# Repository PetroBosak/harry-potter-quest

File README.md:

# Квест «Гаррі Поттер» — Сортувальний капелюх

Нова електроніка для шапки зі старого квесту. Плата та сама, що в щитах LaserX «6-7»
(репозиторій [challenge-duel](https://github.com/PetroBosak/challenge-duel), варіант плати `hat`),
плюс вихід на мотор «рота».

## Що робить шапка
Так само, як стара прошивка (`ref/hate_hogrards.ino`, Arduino + DFPlayer + реле):

| Кнопка брелока | Фрази (по колу) | Світло |
|---|---|---|
| Грифіндор | 0001…0007 | червоний з золотими іскрами |
| Слизерин | 0008…0014 | зелений зі срібними іскрами |
| Старт | 0015…0016 | фіолетовий / синій |
| Фінал | 0017…0018 | золотий |

- Мотор ворушить «рот» у такт фразі за таблицями зі старої прошивки (`firmware/hat/mouth.h`).
  Замість реле тепер транзистор: плавний старт (ШІМ 20 кГц), потужність задається в `config.h`.
- Нова кнопка брелока перебиває поточну фразу.
- **Кнопка на шапці** (J3): замовкнути (звук, мотор і світло зупиняються).
- Чекаючи, капелюх ледь «дихає» фіолетовим (якщо підключена стрічка).
- Коди старого брелока вже вписані, тож він працює одразу. **Інший брелок:** увімкнути шапку
  з затиснутою кнопкою, далі натиснути на брелоку по черзі Грифіндор → Слизерин → Старт → Фінал.
  Після кожної кнопки мотор коротко смикнеться, коди збережуться в пам'яті.

## Залізо
- Плата: [`pcb/`](pcb/) — гербери для замовлення, BOM, схема, KiCad (50×50 мм): ESP32-C3 SuperMini, MAX98357A,
  приймач SYN480R, ключ мотора AO3400A на GPIO20 з захисним діодом SS34.
- Схема підключення: [`docs/wiring-hat.png`](docs/wiring-hat.png) (генерує `docs/tools/wiring_hat.py`).
- Та сама плата йде й на **мандрагору** (пищалка, коли піднімають іграшку): модуль заряду J5019 на звороті,
  клемники АКУМ і ЗАРЯДКА — див. [`pcb/README.md`](pcb/README.md#мандрагора-живлення-від-акумулятора).
- Роз'єми: J1 блок 5 В (**XT30PW-M** на платі, XT30U-F на дроті блока; захисту від переполюсовки немає) ·
  клемники J2 стрічка WS2812B · J3 кнопка · J4 друга стрічка (необов'язково) · **J5 МОТОР (M+ / M−)** ·
  J6 передавач FS1000A (TX = GPIO21, 5V, GND; на майбутнє, прошивка його не використовує) ·
  динамік — у клеми модуля MAX98357A.
- C1 — SMD-електроліт 1000 мкФ 10 В, 10×10,5 мм (Hitano ELV102M10RF): конденсатор із виводами на цю плату не встане.
- Замовлення: панель 2×2 `pcb/panel-hat-gerber.zip` або одна плата `pcb/shield67-hat-gerber.zip`; деталі й пайка — [`pcb/README.md`](pcb/README.md).
- Мотор **на 5 В** (підтверджено замовником), живиться від +5 В блока. Ключ витримує кілька ампер.

## Звуки
Звуки вбудовані в прошивку, SD-картка і DFPlayer не потрібні.
`firmware/sounds/0001…0018.mp3` → `python firmware/tools/gen_sounds.py` → `firmware/hat/sounds.h`
(IMA ADPCM, 16 кГц; усі 18 фраз ≈ 1,5 МБ). Потрібен `ffmpeg`.
Новий трек: покласти mp3 з потрібним номером, перегенерувати `sounds.h`, за потреби поправити `mouth.h`
і групи в `config.h`, перепрошити.

## Прошивка
Бібліотеки: **FastLED 3.9.20** (не 3.10.x, вона не компілюється під C3), **rc-switch**.
Ядро `esp32:esp32` (3.x або 2.0.17).

```bash
arduino-cli compile --fqbn esp32:esp32:esp32c3:PartitionScheme=huge_app,CDCOnBoot=cdc --upload -p COMx firmware/hat
```

Монітор: `arduino-cli monitor -p COMx -c baudrate=115200`. Там видно коди брелока й номери фраз.
Нова SuperMini не прошивається: затиснути BOOT, натиснути й відпустити RST, відпустити BOOT.

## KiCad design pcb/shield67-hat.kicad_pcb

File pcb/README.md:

# Плата шапки (50 × 50 мм)

Плата під ESP32-C3 SuperMini — та сама, що в щитах LaserX «6-7», варіант `hat`: плюс ключ мотора «рота»,
а на звороті — місце під модуль заряду J5019 для мандрагори (від акумулятора).

| Файл | Що це |
|---|---|
| `shield67-hat-gerber.zip` | **для замовлення** (JLCPCB, PCBWay…): завантажити zip як є, 2 шари, 1,6 мм |
| `gerber-hat/` | ті самі гербери й свердління, розпаковані |
| `BOM-hat.csv` | список деталей |
| `shield67-hat-schematic.pdf` | принципова схема |
| `render-top-hat.png`, `render-bottom-hat.png`, `routing-hat.png` | як виглядає плата і доріжки |
| `shield67-hat.kicad_*`, `lib/`, `*-lib-table` | проєкт KiCad 10 (відкривати `shield67-hat.kicad_pro`) |

## Замовлення: панель 2×2 = 4 плати на 100×100 мм
Мінімальне замовлення 5 шт. → 5 панелей = **20 плат** — на всі атракціони (шапка, щити тощо: та сама плата, різні деталі розпаюються).

| Файл | Що це |
|---|---|
| `panel-hat-gerber.zip` | **для замовлення панеллю** |
| `gerber-panel-hat/`, `panel-hat.kicad_pcb` | те саме розпаковане / KiCad |
| `render-top-panel-hat.png` | як виглядає панель |

Як замовляти на JLCPCB: завантажити `panel-hat-gerber.zip`, розмір визначиться **100 × 100 мм**, далі
**Delivery Format / Panel: «Panel by Customer»**, **Panel Format: V-cut** (лінії V-cut — посередині по x і y, у шарі контуру),
кількість **5**. Шари 2, товщина 1,6 мм, решта — за замовчуванням.
Мідь від лінії V-cut — 0,5 мм (вимога JLCPCB ≥ 0,4). Плати ламаються руками по V-cut, потім паяються.

Під щит «6-7» мотор не потрібен: Q1, R7, R8, D2, C5, J5 не паяти. На шапці й щитах U6, J7, J8 (зворот) не паяти.

## Роз'єми
| | Що підключати |
|---|---|
| **J1** XT30PW-M | блок живлення **5 В** (на дроті — XT30U-F). Захисту від переполюсовки немає |
| **J2** | стрічка WS2812B (GPIO10) |
| **J3** | кнопка на шапці (GPIO5 → GND) |
| **J4** | друга стрічка (GPIO7), необов'язково |
| **J5 МОТОР** | M+ = +5 В, M− = ключ Q1 AO3400A (GPIO20), діод SS34 паралельно мотору |
| **J6** | передавач FS1000A (TX = GPIO21, 5V, GND), на майбутнє |
| **J7** АКУМ (зворот) | лише мандрагора: акумулятор Li-ion 3,7 В, «+» — верхній вивід; вимикач — у дроті «+» |
| **J8** ЗАРЯДКА 5 В (зворот) | лише мандрагора: гніздо зарядки 5 В (на стінці відра) → IN+/IN− модуля, «+» — верхній |
| динамік | у клеми модуля MAX98357A |

Приймач — SYN480R 433 МГц, антена — дріт 17,3 см у пад **ANT**. Отворів кріплення 2 (угорі).

## Мандрагора: живлення від акумулятора

- **U6 — модуль J5019** (заряд Li-ion + підвищувач до 5 В) на **звороті**, на штирях 2,54 мм крізь 6 отворів:
  BAT−, BAT+, IN−, IN+, VOUT−, VOUT+. Отвори овальні (допуск ±0,6 мм). Відстані між отворами (виміряв замовник):
  BAT−↔BAT+ 9,2 мм, VOUT−↔VOUT+ 7,0, IN−↔IN+ 16, IN+↔VOUT− 6,8, BAT+↔VOUT− уздовж 10, ряди 20.
- Перед пайкою **роздрукувати `mandrake-back-1to1.pdf` у масштабі 100 %** і прикласти модуль: отвори мають збігтися.
- Висновки SuperMini і MAX98357A під модулем підрізати коротко; штирі модуля, що виходять на лице під модулі, — теж.
- Підвищувач J5019 **до пайки виставити на 5,0 В** (підстроювач на модулі, тестером на VOUT).
- **XT30 (J1) у мандрагорі не паяти**: це вхід 5 В на рейку плати, а не зарядка. Зарядка — тільки через **J8**.
- Пищалка (активна, 5 В) — на **J5** (M+ / M−), датчик (геркон / Холл / мікроперемикач) — на **J3**.

## Як паяти
1. Спершу SMD: U4, U5 (ключ — вивід 1), Q1, R1–R8, C2–C6, D1 і D2 (**смужка — катод**), C1.
   **C1** — SMD-електроліт 1000 мкФ 10 В, 10×10,5 мм (Hitano ELV102M10RF): **чорна мітка на корпусі — мінус, праворуч**, зрізані кути основи — до «+» ліворуч.
2. Гребінки «мама»: 2 × 1×8 (SuperMini), 1×7 (MAX98357A), 1×4 (SYN480R) — вставити в модулі й паяти разом із ними.
3. Клемники, XT30 (у мандрагорі — замість XT30 модуль J5019 і клемники J7, J8 на звороті).
4. Тестером: +5V ↔ GND немає КЗ; на 5V SuperMini після D1 ≈ 4,7 В від блока.

## Звідки файли
Плату генерує скрипт у репозиторії [challenge-duel](https://github.com/PetroBosak/challenge-duel/tree/claude/relaxed-gauss-k7b976/pcb)
(`SHIELD67_VARIANT=hat python pcb/tools/build.py --export`). Правки — там, потім скопіювати сюди файли `*-hat*`.

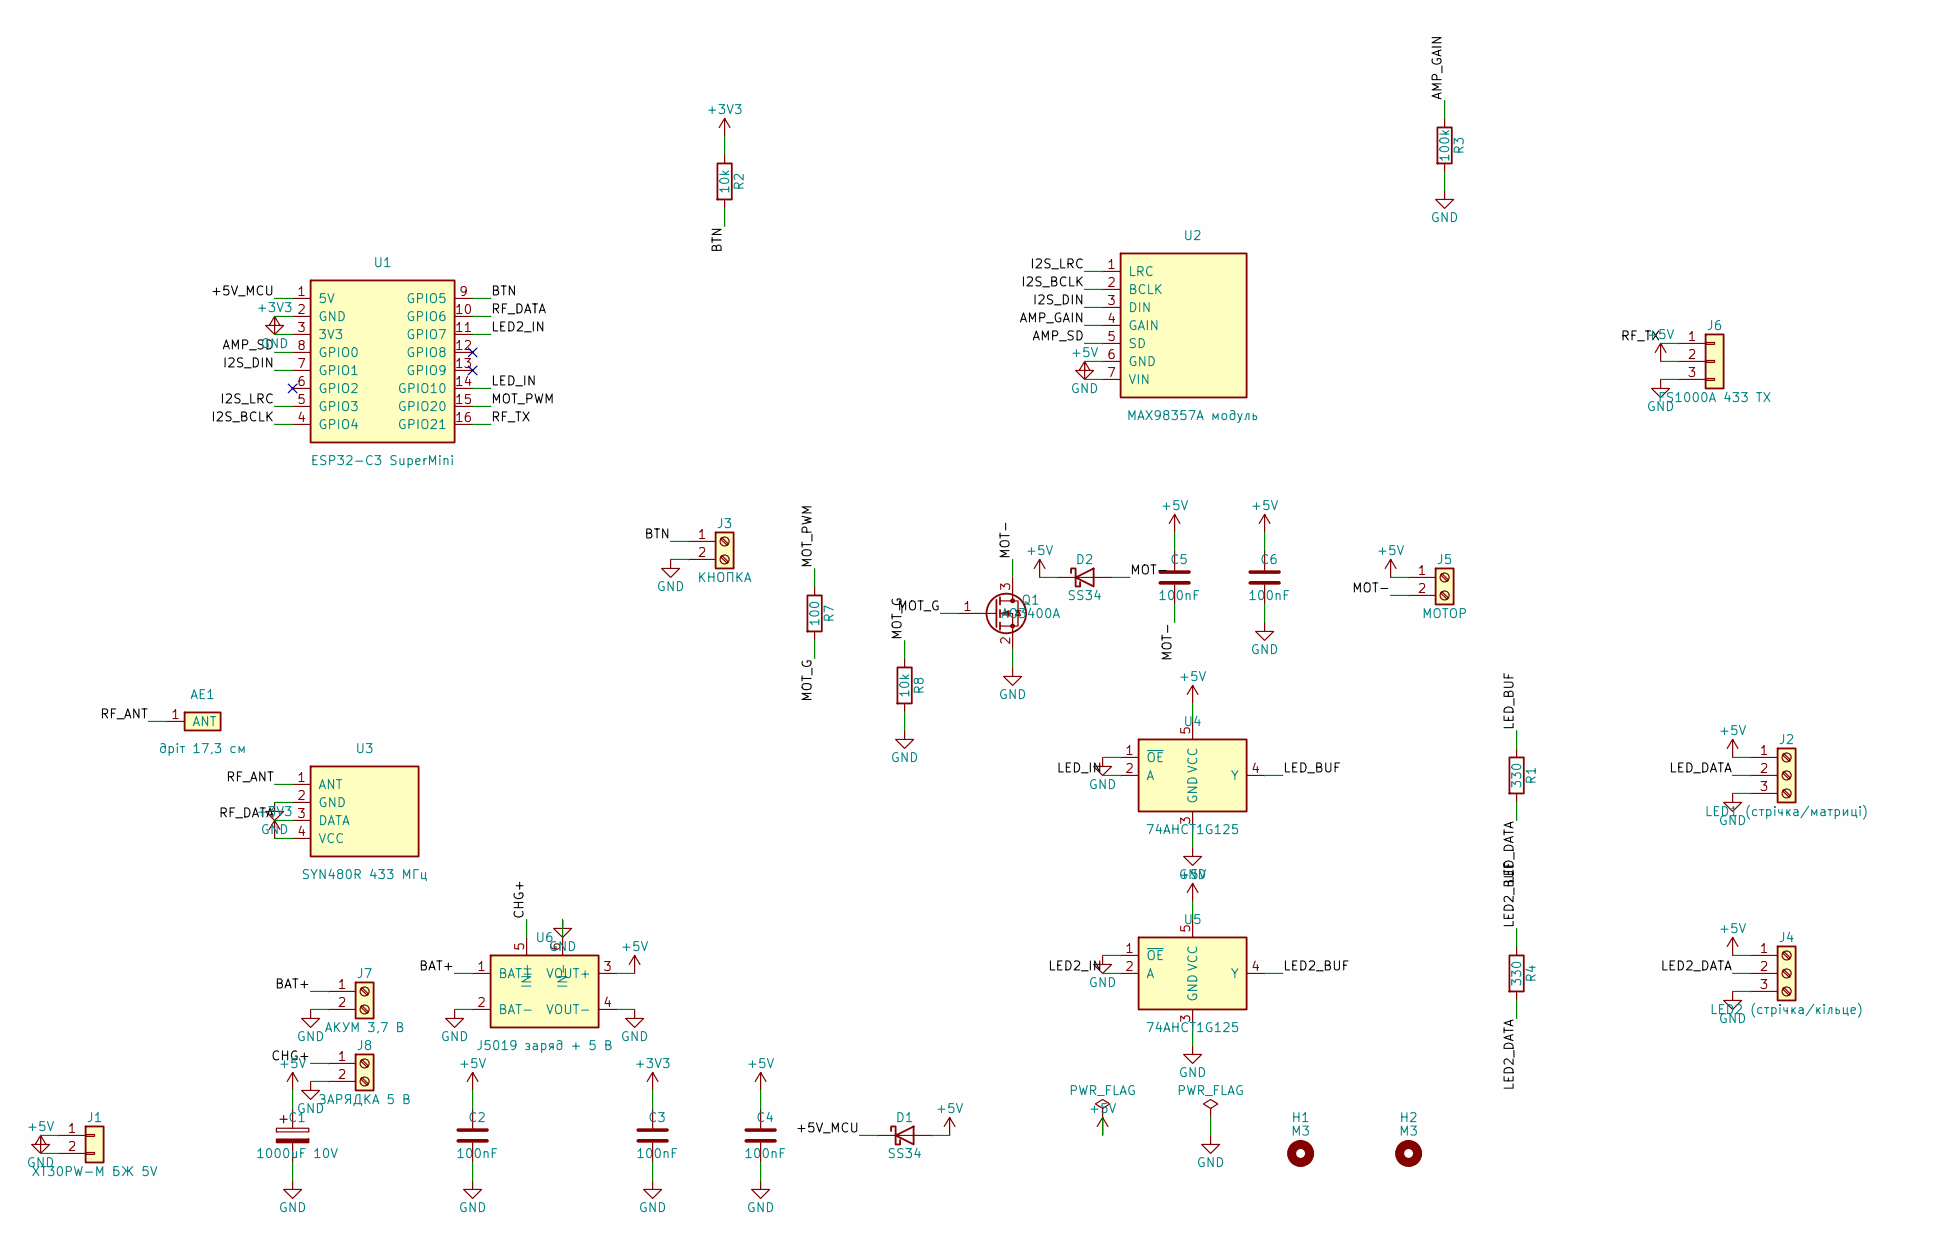
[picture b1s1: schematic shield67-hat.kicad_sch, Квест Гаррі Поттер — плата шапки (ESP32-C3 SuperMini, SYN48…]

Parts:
AE1: дріт 17,3 см; ANT_Wire_Pad
C1: 1000uF 10V; CP_Elec_10x10.5
C2, C3, C4, C5, C6: 100nF; C_0805_2012Metric
D1, D2: SS34; D_SMA
H1, H2: M3; MountingHole_3.2mm_M3
J1: XT30PW-M БЖ 5V; AMASS_XT30PW-M_1x02_P2.50mm_Horizontal
J2: LED1 (стрічка/матриці); TerminalBlock_Phoenix_PT-1,5-3-3.5-H_1x03_P3.50mm_Horizontal
J3: КНОПКА; TerminalBlock_Phoenix_PT-1,5-2-3.5-H_1x02_P3.50mm_Horizontal
J4: LED2 (стрічка/кільце); TerminalBlock_Phoenix_PT-1,5-3-3.5-H_1x03_P3.50mm_Horizontal
J5: МОТОР; TerminalBlock_Phoenix_PT-1,5-2-3.5-H_1x02_P3.50mm_Horizontal
J6: FS1000A 433 TX; PinHeader_1x03_P2.54mm_Vertical
J7: АКУМ 3,7 В; TerminalBlock_Phoenix_PT-1,5-2-3.5-H_1x02_P3.50mm_Horizontal
J8: ЗАРЯДКА 5 В; TerminalBlock_Phoenix_PT-1,5-2-3.5-H_1x02_P3.50mm_Horizontal
Q1: AO3400A; SOT-23
R1, R4: 330; R_0805_2012Metric
R2, R8: 10k; R_0805_2012Metric
R3: 100k; R_0805_2012Metric
R7: 100; R_0805_2012Metric
U1: ESP32-C3 SuperMini; ESP32-C3_SuperMini_Socket
U2: MAX98357A модуль; MAX98357A_Module_Socket
U3: SYN480R 433 МГц; SYN480R_Socket
U4, U5: 74AHCT1G125; SOT-23-5
U6: J5019 заряд + 5 В; J5019_Back

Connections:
+3V3: C3.1, R2.1, U1.3 (3V3), U3.4 (VCC)
+5V: C1.1, C2.1, C4.1, C5.1, C6.1, D1.2 (A), D2.1 (K), J1.2, J2.1, J4.1, J5.1, J6.2, U2.7 (VIN), U4.5 (VCC), U5.5 (VCC), U6.3 (VOUT+)
/+5V_MCU: D1.1 (K), U1.1 (5V)
/AMP_GAIN: R3.1, U2.4 (GAIN)
/AMP_SD: U1.8 (GPIO0), U2.5 (SD)
/BAT+: J7.1, U6.1 (BAT+)
/BTN: J3.1, R2.2, U1.9 (GPIO5)
/CHG+: J8.1, U6.5 (IN+)
/I2S_BCLK: U1.4 (GPIO4), U2.2 (BCLK)
/I2S_DIN: U1.7 (GPIO1), U2.3 (DIN)
/I2S_LRC: U1.5 (GPIO3), U2.1 (LRC)
/LED2_BUF: R4.1, U5.4 (Y)
/LED2_DATA: J4.2, R4.2
/LED2_IN: U1.11 (GPIO7), U5.2 (A)
/LED_BUF: R1.1, U4.4 (Y)
/LED_DATA: J2.2, R1.2
/LED_IN: U1.14 (GPIO10), U4.2 (A)
/MOT-: C5.2, D2.2 (A), J5.2, Q1.3 (D)
/MOT_G: Q1.1 (G), R7.2, R8.1
/MOT_PWM: R7.1, U1.15 (GPIO20)
/RF_ANT: AE1.1, U3.1 (ANT)
/RF_DATA: U1.10 (GPIO6), U3.3 (DATA)
/RF_TX: J6.1, U1.16 (GPIO21)
GND: C1.2, C2.2, C3.2, C4.2, C6.2, J1.1, J2.3, J3.2, J4.3, J6.3, J7.2, J8.2, Q1.2 (S), R3.2, R8.2, U1.2 (GND), U2.6 (GND), U3.2 (GND), U4.1 (~OE), U4.3 (GND), U5.1 (~OE), U5.3 (GND), U6.2 (BAT-), U6.4 (VOUT-), U6.6 (IN-)

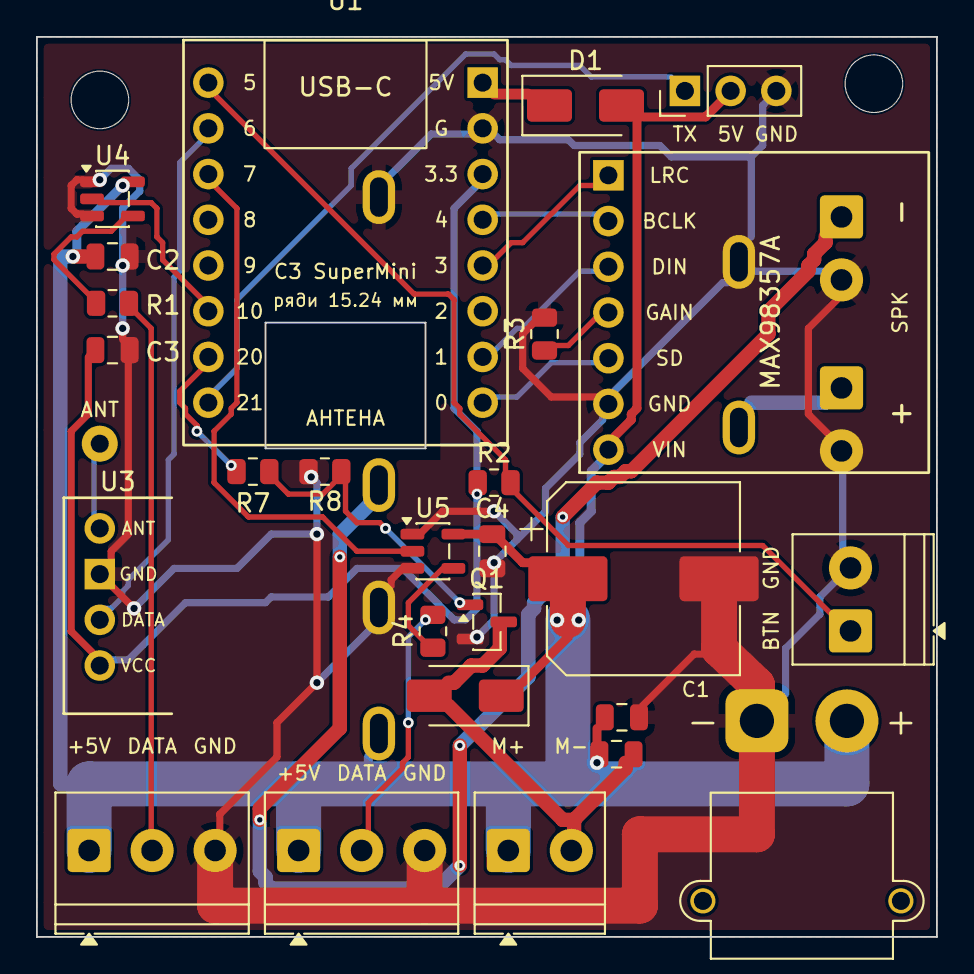
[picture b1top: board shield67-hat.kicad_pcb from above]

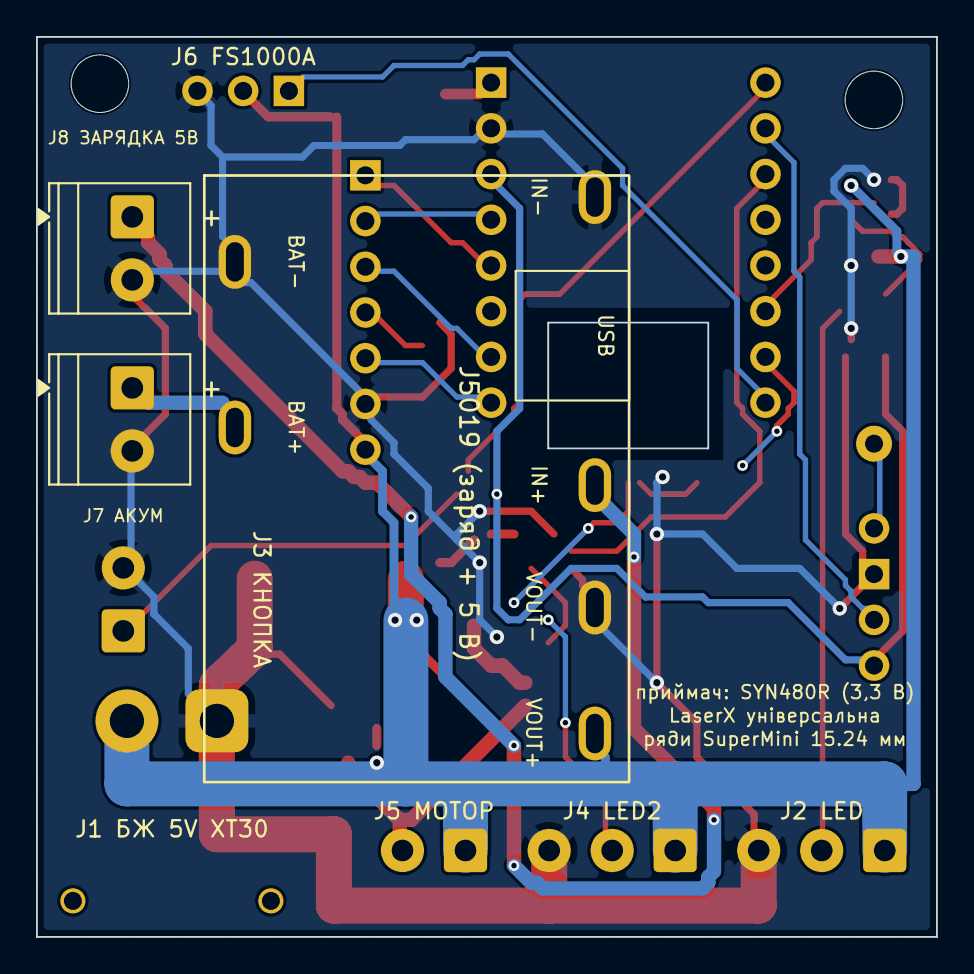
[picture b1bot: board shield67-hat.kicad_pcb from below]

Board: 2 copper layers, 50.0 x 50.0 mm, 32 parts (3 on the bottom side), 24 nets.

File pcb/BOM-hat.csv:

"Позиції","Номінал","Посадкове місце","Кількість"
"AE1","дріт 17,3 см","shield67:ANT_Wire_Pad","1"
"C1","1000uF 10V","Capacitor_SMD:CP_Elec_10x10.5","1"
"C2-C6","100nF","Capacitor_SMD:C_0805_2012Metric","5"
"D1,D2","SS34","Diode_SMD:D_SMA","2"
"J1","XT30PW-M БЖ 5V","Connector_AMASS:AMASS_XT30PW-M_1x02_P2.50mm_Horizontal","1"
"J2","LED1 (стрічка/матриці)","TerminalBlock_Phoenix:TerminalBlock_Phoenix_PT-1,5-3-3.5-H_1x03_P3.50mm_Horizontal","1"
"J3","КНОПКА","TerminalBlock_Phoenix:TerminalBlock_Phoenix_PT-1,5-2-3.5-H_1x02_P3.50mm_Horizontal","1"
"J4","LED2 (стрічка/кільце)","TerminalBlock_Phoenix:TerminalBlock_Phoenix_PT-1,5-3-3.5-H_1x03_P3.50mm_Horizontal","1"
"J5","МОТОР","TerminalBlock_Phoenix:TerminalBlock_Phoenix_PT-1,5-2-3.5-H_1x02_P3.50mm_Horizontal","1"
"J6","FS1000A 433 TX","Connector_PinHeader_2.54mm:PinHeader_1x03_P2.54mm_Vertical","1"
"J7","АКУМ 3,7 В","TerminalBlock_Phoenix:TerminalBlock_Phoenix_PT-1,5-2-3.5-H_1x02_P3.50mm_Horizontal","1"
"J8","ЗАРЯДКА 5 В","TerminalBlock_Phoenix:TerminalBlock_Phoenix_PT-1,5-2-3.5-H_1x02_P3.50mm_Horizontal","1"
"Q1","AO3400A","Package_TO_SOT_SMD:SOT-23","1"
"R1,R4","330","Resistor_SMD:R_0805_2012Metric","2"
"R2,R8","10k","Resistor_SMD:R_0805_2012Metric","2"
"R3","100k","Resistor_SMD:R_0805_2012Metric","1"
"R7","100","Resistor_SMD:R_0805_2012Metric","1"
"U1","ESP32-C3 SuperMini","shield67:ESP32-C3_SuperMini_Socket","1"
"U2","MAX98357A модуль","shield67:MAX98357A_Module_Socket","1"
"U3","SYN480R 433 МГц","shield67:SYN480R_Socket","1"
"U4,U5","74AHCT1G125","Package_TO_SOT_SMD:SOT-23-5","2"
"U6","J5019 заряд + 5 В","shield67:J5019_Back","1"
"U1","Гребінка мама 1x8, крок 2,54, пряма","—","2"
"U2","Гребінка мама 1x7, крок 2,54, пряма","—","1"
"U3","Гребінка мама 1x4, крок 2,54, пряма","—","1"

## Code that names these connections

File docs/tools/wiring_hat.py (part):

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
# ---- ESP32-C3 SuperMini ----
box(480, 190, 160, 320, 'ESP32-C3', 'SuperMini', '#eef6ff')
L = {'GND': 260, 'GPIO6': 300, '3V3': 340, 'GPIO5': 380, 'GPIO20': 470, 'GPIO21': 495}   # у порядку виводів SYN480R
R = {'5V': 230, 'GND ': 262, 'GPIO10': 300, 'GPIO7': 330, 'GPIO4': 380, 'GPIO3': 420, 'GPIO1': 460, 'GPIO0': 490}
SILK = {'3V3': '3.3', 'GND': 'G', 'GND ': 'G', '5V': '5V'}   # як надруковано на платі SuperMini
for side, pins, x in (('l', L, 480), ('r', R, 640)):
    for n, y in pins.items():
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box(1110, 545, 80, 60, 'AO3400A', 'Q1, SOT-23')
text(MX0 + 8, 541, 'D', 10, weight='700'); text(1104, 580, 'G', 10, 'end', weight='700'); text(MX0 + 6, 620, 'S', 10, weight='700')
wire([(MX0, 605), (MX0, BOTG)], BLK); dot(MX0, BOTG, BLK)
# GPIO20 → 100 Ом → затвор; 10 кОм затвор → GND
wire([(480, 470), (450, 470), (450, 590), (1110, 590)], SIG, 'GPIO20 → мотор (ШІМ 20 кГц)', 460, 584)
resistor(1040, 1100, 590, '100 Ом', SIG)
dot(1020, 590, SIG)
wire([(1020, 590), (1020, 600)], SIG, width=2)
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notes = [
    'Крапка = з\'єднання. Перетин без крапки = дроти не з\'єднані. Так само розведена плата pcb/shield67-hat.',
    'Живлення: роз\'єм J1 XT30PW-M на платі, XT30U-F на дроті блока. Захисту від переполюсовки немає. Усі GND спільні; мотор і стрічки — від +5 В блока, не від ESP32.',
    'Мотор: GPIO20 → 100 Ом → затвор AO3400A, 10 кОм затвор → GND (мотор стоїть, поки ESP стартує). Мотор — між M+ (+5 В) і M− (стік), J5.',
    'SS34 паралельно мотору (катод до +5 В) гасить кидок від мотора; 100 нФ на клемах (ще один варто припаяти прямо на мотор).',
    'SYN480R: VCC → 3,3 В, DAT → GPIO6, ANT → провід 17,3 см. Кнопка J3: GPIO5 → кнопка → GND (підтяжка 10 кОм на платі).',
    'Стрічка WS2812B: GPIO10 → U4 → 330 Ом → J2. Друга (необов\'язково): GPIO7 → U5 → 330 Ом → J4. Кількість — LED_COUNT / LED2_COUNT у config.h.',
    'MAX98357A: динамік на «+» і «−» (НЕ на GND), GAIN через 100 кОм на GND = 15 дБ. Діод SS34 (D1): можна разом блок і USB ноутбука.',
    'J6 — передавач FS1000A (TX = GPIO21, 5V, GND), на майбутнє: прошивка шапки його не використовує, можна не ставити.',
    'Увімкнути шапку з затиснутою кнопкою → навчання брелока (Грифіндор, Слизерин, Старт, Фінал). Кнопка в роботі — замовкнути.',
]
for i, n in enumerate(notes):
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
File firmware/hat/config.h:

// =====================================================================
//  Налаштування шапки «Сортувальний капелюх» (квест «Гаррі Поттер»)
// =====================================================================
#pragma once

// ---- Піни ESP32-C3 SuperMini (плата challenge-duel/pcb, варіант hat; схема docs/wiring-hat.png) ----
// GPIO 2, 8, 9 не використовуємо — від них залежить старт плати.
// GPIO 21 — TX завантажувача (смикається при старті), тому мотор саме на GPIO 20.
#define PIN_MOTOR    20   // ключ мотора: AO3400A через 100 Ом (J5 МОТОР)
#define PIN_LEDS     10   // стрічка WS2812B (U4 → 330 Ом → J2 LED)
#define PIN_LEDS2     7   // друга стрічка / «очі» (U5 → 330 Ом → J4 LED2)
#define PIN_BUTTON    5   // кнопка (NO → GND, підтяжка 10 кОм до 3V3) — J3
#define PIN_RF        6   // приймач 433 МГц SYN480R, DATA
#define PIN_RF_TX    21   // J6: FS1000A TX. Прошивка тримає LOW, щоб передавач не глушив приймач
#define PIN_I2S_BCLK  4   // MAX98357A BCLK
#define PIN_I2S_LRC   3   // MAX98357A LRC
#define PIN_I2S_DIN   1   // MAX98357A DIN
#define PIN_AMP_SD    0   // MAX98357A SD: HIGH = грає, LOW = вимкнений (без шипіння)

// ---- Мотор («рот» капелюха) ----
#define MOTOR_DUTY     100   // потужність мотора, % (менше — повільніше / тихіше)
#define MOTOR_RAMP_MS   80   // плавний старт: за стільки мс від 0 до MOTOR_DUTY
#define MOTOR_FREQ   20000   // частота ШІМ, Гц (20 кГц — не пищить)
#define MOUTH_DELAY_MS 100   // рот починає рухатись через стільки мс після старту фрази (як у старій шапці)

// ---- Світло (0 = стрічки немає) ----
#define LED_COUNT     16    // світлодіодів на J2 (GPIO10)
#define LED2_COUNT     0    // світлодіодів на J4 (GPIO7), напр. 2 «очі»
#define BRIGHTNESS   120    // 0–255
#define MAX_MILLIAMPS 1500  // ліміт струму світлодіодів, мА
#define HOUSE_GLOW_MS 4000  // після фрази факультету капелюх світиться його кольором ще стільки мс

// ---- Звук: вбудований у прошивку (firmware/sounds/*.mp3 → sounds.h) ----
#define VOLUME 100          // 0–100 %. Грубіше — резистором GAIN на MAX98357A

// ---- Фрази: групи треків. Кожне натискання — наступна фраза групи по колу ----
#define GRYFFINDOR_FIRST  1   // 0001…0007 — Грифіндор
#define GRYFFINDOR_LAST   7
#define SLYTHERIN_FIRST   8   // 0008…0014 — Слизерин
#define SLYTHERIN_LAST   14
#define START_FIRST      15   // 0015…0016 — привітання / початок
#define START_LAST       16
#define FINISH_FIRST     17   // 0017…0018 — фінал
#define FINISH_LAST      18

// ---- Брелок 433 МГц ----
// Коди кнопок старого брелока (зі старої прошивки hate_hogrards.ino) — працюють одразу.
// Інший брелок: увімкнути шапку з затиснутою кнопкою і натиснути на брелоку по черзі
// Грифіндор → Слизерин → Старт → Фінал (коди збережуться в пам'яті).
#define FOB_GRYFFINDOR 753828
#define FOB_SLYTHERIN  753826
#define FOB_START      753832
#define FOB_FINISH     753825
#define RF_REPEAT_MS     800  // повтор тієї ж кнопки швидше — ігнорується (брелок шле код кілька разів)
